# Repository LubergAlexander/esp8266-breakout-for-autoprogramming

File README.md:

# Description

Test esp8266 breakout board with an autoprogramming header.

# 3D Render

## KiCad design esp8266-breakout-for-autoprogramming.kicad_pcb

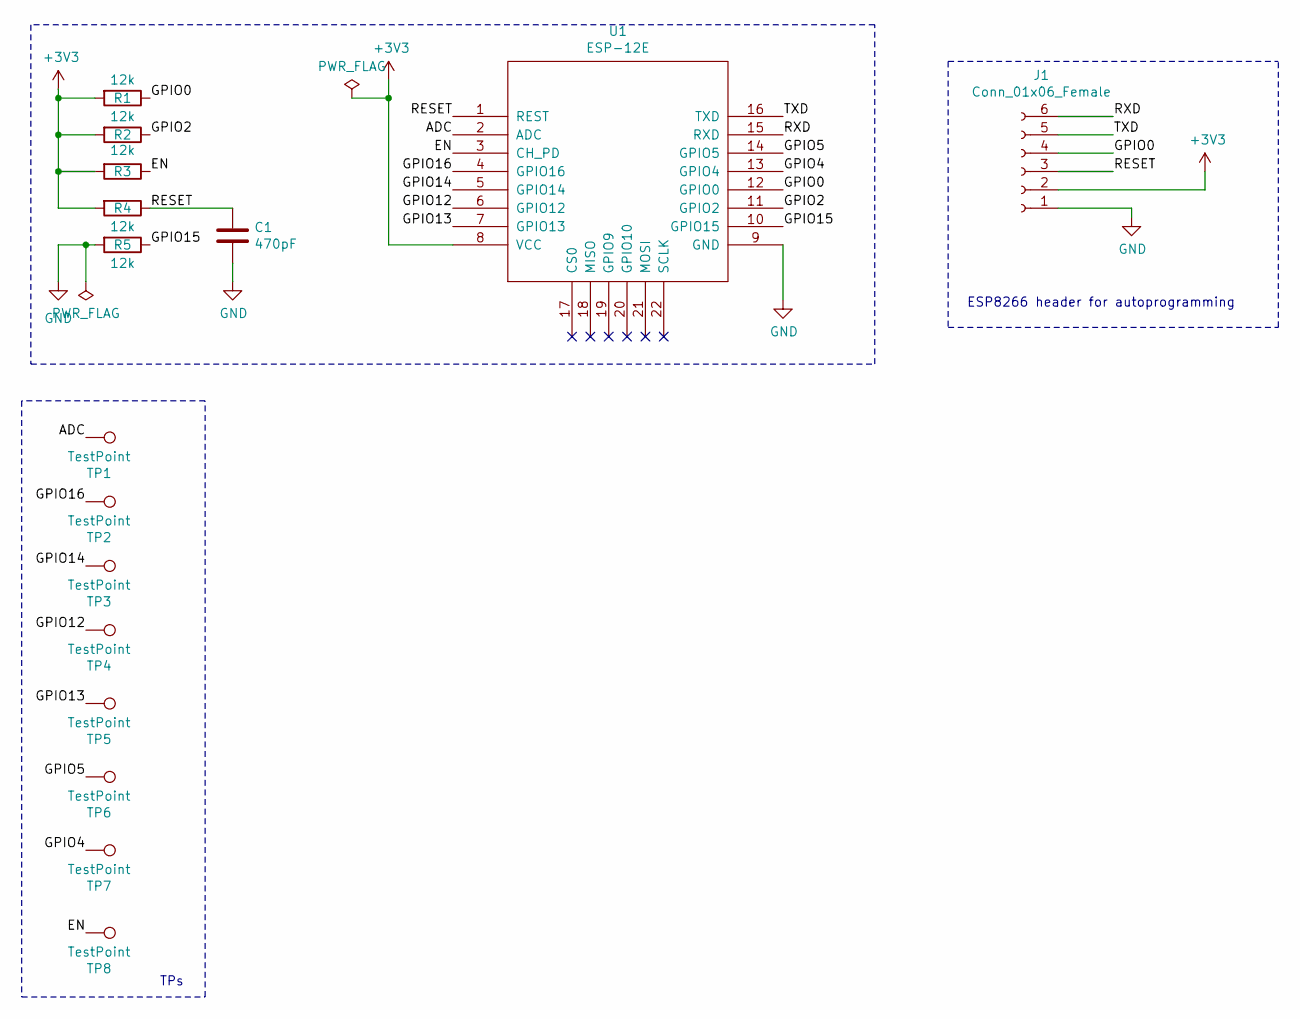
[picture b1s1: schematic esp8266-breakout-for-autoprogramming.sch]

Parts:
C1: 470pF; C_0805_2012Metric
J1: Conn_01x06_Female; PinSocket_1x06_P2.54mm_Horizontal
R1, R2, R3, R4, R5: 12k; R_0805_2012Metric
TP1, TP2, TP3, TP4, TP5, TP6, TP7, TP8: TestPoint; TestPoint_Pad_D1.0mm
U1: ESP-12E; ESP-12E_SMD

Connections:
+3V3: J1.2, R1.2, R2.2, R3.2, R4.2, U1.8 (VCC)
/ADC: TP1.1, U1.2 (ADC)
/EN: R3.1, TP8.1, U1.3 (CH_PD)
/GPIO0: J1.4, R1.1, U1.12 (GPIO0)
/GPIO2: R2.1, U1.11 (GPIO2)
/GPIO4: TP7.1, U1.13 (GPIO4)
/GPIO5: TP6.1, U1.14 (GPIO5)
/GPIO12: TP4.1, U1.6 (GPIO12)
/GPIO13: TP5.1, U1.7 (GPIO13)
/GPIO14: TP3.1, U1.5 (GPIO14)
/GPIO15: R5.1, U1.10 (GPIO15)
/GPIO16: TP2.1, U1.4 (GPIO16)
/RESET: C1.1, J1.3, R4.1, U1.1 (REST)
/RXD: J1.6, U1.15 (RXD)
/TXD: J1.5, U1.16 (TXD)
GND: C1.2, J1.1, R5.2, U1.9 (GND)

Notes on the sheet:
ESP8266 header for autoprogramming
TPs

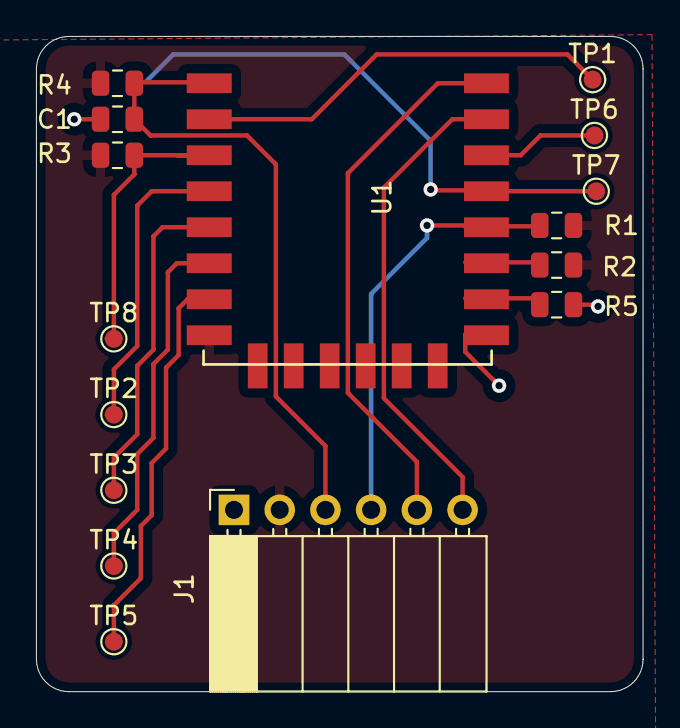
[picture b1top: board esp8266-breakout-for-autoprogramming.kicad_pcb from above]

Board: 2 copper layers, 33.7 x 36.4 mm, 16 parts (0 on the bottom side), 16 nets.

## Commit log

2020-01-03 Init
2020-01-04 Breakout board
2020-01-04 cleanup
2020-01-04 Fixed ERC
2020-01-04 Added pic
